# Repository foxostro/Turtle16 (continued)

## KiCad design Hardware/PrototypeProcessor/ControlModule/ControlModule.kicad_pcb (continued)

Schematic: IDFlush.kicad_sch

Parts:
C2, C3, C4, C17: 0.1uF; C_0603_1608Metric_Pad1.08x0.95mm_HandSolder
U1, U18: 74HC245; TSSOP-20_4.4x6.5mm_P0.65mm
U2, U17: 74AHCT16245; TSSOP-48_6.1x12.5mm_P0.5mm

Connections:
/ID/Ctl_Mid0: U17.47 (1A1); also elsewhere on the board
/ID/Ctl_Mid1: U17.46 (1A2); also elsewhere on the board
/ID/Ctl_Mid2: U17.44 (1A3); also elsewhere on the board
/ID/Ctl_Mid3: U17.43 (1A4); also elsewhere on the board
/ID/Ctl_Mid4: U17.41 (1A5); also elsewhere on the board
/ID/Ctl_Mid5: U17.40 (1A6); also elsewhere on the board
/ID/Ctl_Mid6: U17.38 (1A7); also elsewhere on the board
/ID/Ctl_Mid7: U17.37 (1A8); also elsewhere on the board
/ID/Ctl_Mid8: U17.36 (2A1); also elsewhere on the board
/ID/Ctl_Mid9: U17.35 (2A2); also elsewhere on the board
/ID/Ctl_Mid10: U17.33 (2A3); also elsewhere on the board
/ID/Ctl_Mid11: U17.32 (2A4); also elsewhere on the board
/ID/Ctl_Mid12: U17.30 (2A5); also elsewhere on the board
/ID/Ctl_Mid13: U17.29 (2A6); also elsewhere on the board
/ID/Ctl_Mid14: U17.27 (2A7); also elsewhere on the board
/ID/Ctl_Mid15: U17.26 (2A8); also elsewhere on the board
/ID/Ctl_Mid16: U18.11 (B7); also elsewhere on the board
/ID/Ctl_Mid17: U18.12 (B6); also elsewhere on the board
/ID/Ctl_Mid18: U18.13 (B5); also elsewhere on the board
/ID/Ctl_Mid19: U18.14 (B4); also elsewhere on the board
/ID/Ctl_Mid20: U18.15 (B3); also elsewhere on the board
/ID/Ctl_Mid21: U18.16 (B2); also elsewhere on the board
/ID/Ctl_Mid22: U18.17 (B1); also elsewhere on the board
/ID/Ctl_Mid23: U18.18 (B0); also elsewhere on the board
/ID/Hazard Control/FLUSH: U17.25 (2~OE), U17.48 (1~OE), U18.19 (CE); also elsewhere on the board
/ID/Hazard Control/~FLUSH: U1.19 (CE), U2.25 (2~OE), U2.48 (1~OE); also elsewhere on the board
/ID/ID Flush/Ctl_ID0: U2.47 (1A1), U17.2 (1B1); also elsewhere on the board
/ID/ID Flush/Ctl_ID1: U2.46 (1A2), U17.3 (1B2); also elsewhere on the board
/ID/ID Flush/Ctl_ID2: U2.44 (1A3), U17.5 (1B3); also elsewhere on the board
/ID/ID Flush/Ctl_ID3: U2.43 (1A4), U17.6 (1B4); also elsewhere on the board
/ID/ID Flush/Ctl_ID4: U2.41 (1A5), U17.8 (1B5); also elsewhere on the board
/ID/ID Flush/Ctl_ID5: U2.40 (1A6), U17.9 (1B6); also elsewhere on the board
/ID/ID Flush/Ctl_ID6: U2.38 (1A7), U17.11 (1B7); also elsewhere on the board
/ID/ID Flush/Ctl_ID7: U2.37 (1A8), U17.12 (1B8); also elsewhere on the board
/ID/ID Flush/Ctl_ID8: U2.36 (2A1), U17.13 (2B1); also elsewhere on the board
/ID/ID Flush/Ctl_ID9: U2.35 (2A2), U17.14 (2B2); also elsewhere on the board
/ID/ID Flush/Ctl_ID10: U2.33 (2A3), U17.16 (2B3); also elsewhere on the board
/ID/ID Flush/Ctl_ID11: U2.32 (2A4), U17.17 (2B4); also elsewhere on the board
/ID/ID Flush/Ctl_ID12: U2.30 (2A5), U17.19 (2B5); also elsewhere on the board
/ID/ID Flush/Ctl_ID13: U2.29 (2A6), U17.20 (2B6); also elsewhere on the board
/ID/ID Flush/Ctl_ID14: U2.27 (2A7), U17.22 (2B7); also elsewhere on the board
/ID/ID Flush/Ctl_ID15: U2.26 (2A8), U17.23 (2B8); also elsewhere on the board
/ID/ID Flush/Ctl_ID16: U1.11 (B7), U18.9 (A7); also elsewhere on the board
/ID/ID Flush/Ctl_ID17: U1.12 (B6), U18.8 (A6); also elsewhere on the board
/ID/ID Flush/Ctl_ID18: U1.13 (B5), U18.7 (A5); also elsewhere on the board
/ID/ID Flush/Ctl_ID19: U1.14 (B4), U18.6 (A4); also elsewhere on the board
/ID/ID Flush/Ctl_ID20: U1.15 (B3), U18.5 (A3); also elsewhere on the board
/ID/ID Flush/Ctl_ID21: U1.16 (B2), U18.4 (A2); also elsewhere on the board
/ID/ID Flush/Ctl_ID22: U1.17 (B1), U18.3 (A1); also elsewhere on the board
/ID/ID Flush/Ctl_ID23: U1.18 (B0), U18.2 (A0); also elsewhere on the board
GND: C2.2, C3.2, C4.2, C17.2, U1.10 (GND), U2.1 (1DIR), U2.4 (GND), U2.10 (GND), U2.15 (GND), U2.21 (GND), U2.24 (2DIR), U2.28 (GND), U2.34 (GND), U2.39 (GND), U2.45 (GND), U17.4 (GND), U17.10 (GND), U17.15 (GND), U17.21 (GND), U17.28 (GND), U17.34 (GND), U17.39 (GND), U17.45 (GND), U18.1 (A->B), U18.10 (GND); also elsewhere on the board
VCC: C2.1, C3.1, C4.1, C17.1, U1.1 (A->B), U1.2 (A0), U1.3 (A1), U1.4 (A2), U1.5 (A3), U1.6 (A4), U1.7 (A5), U1.8 (A6), U1.9 (A7), U1.20 (VCC), U2.2 (1B1), U2.3 (1B2), U2.5 (1B3), U2.6 (1B4), U2.7 (VCC), U2.8 (1B5), U2.9 (1B6), U2.11 (1B7), U2.12 (1B8), U2.13 (2B1), U2.14 (2B2), U2.16 (2B3), U2.17 (2B4), U2.18 (VCC), U2.19 (2B5), U2.20 (2B6), U2.22 (2B7), U2.23 (2B8), U2.31 (VCC), U2.42 (VCC), U17.1 (1DIR), U17.7 (VCC), U17.18 (VCC), U17.24 (2DIR), U17.31 (VCC), U17.42 (VCC), U18.20 (VCC); also elsewhere on the board

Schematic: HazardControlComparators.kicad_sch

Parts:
C10, C11, C12, C13: 0.1uF; C_0603_1608Metric_Pad1.08x0.95mm_HandSolder
TP34: SEL_B_MATCHES_SEL_C_MEM; TestPoint_Pad_D1.0mm
TP35: SEL_A_MATCHES_SEL_C_MEM; TestPoint_Pad_D1.0mm
TP36: SEL_A_MATCHES_SEL_C_EX; TestPoint_Pad_D1.0mm
TP37: SEL_B_MATCHES_SEL_C_EX; TestPoint_Pad_D1.0mm
U10, U11, U12, U13: 74F521; SOIC-20W_7.5x12.8mm_P1.27mm

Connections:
/ID Prototype Inputs/Ins_ID2: U11.2 (P0), U12.2 (P0); also elsewhere on the board
/ID Prototype Inputs/Ins_ID3: U11.4 (P1), U12.4 (P1); also elsewhere on the board
/ID Prototype Inputs/Ins_ID4: U11.6 (P2), U12.6 (P2); also elsewhere on the board
/ID Prototype Inputs/Ins_ID5: U10.2 (P0), U13.2 (P0); also elsewhere on the board
/ID Prototype Inputs/Ins_ID6: U10.4 (P1), U13.4 (P1); also elsewhere on the board
/ID Prototype Inputs/Ins_ID7: U10.6 (P2), U13.6 (P2); also elsewhere on the board
/ID Prototype Inputs/SelC_MEM0: U12.3 (Q0), U13.3 (Q0); also elsewhere on the board
/ID Prototype Inputs/SelC_MEM1: U12.5 (Q1), U13.5 (Q1); also elsewhere on the board
/ID Prototype Inputs/SelC_MEM2: U12.7 (Q2), U13.7 (Q2); also elsewhere on the board
/ID Prototype Outputs/Ins_EX8: U10.3 (Q0), U11.3 (Q0); also elsewhere on the board
/ID Prototype Outputs/Ins_EX9: U10.5 (Q1), U11.5 (Q1); also elsewhere on the board
/ID Prototype Outputs/Ins_EX10: U10.7 (Q2), U11.7 (Q2); also elsewhere on the board
/ID/Hazard Control/Hazard Control Comparators/SEL_A_MATCHES_SEL_C_EX: TP36.1, U10.19 (~P=Q); also elsewhere on the board
/ID/Hazard Control/Hazard Control Comparators/SEL_A_MATCHES_SEL_C_MEM: TP35.1, U13.19 (~P=Q); also elsewhere on the board
/ID/Hazard Control/Hazard Control Comparators/SEL_B_MATCHES_SEL_C_EX: TP37.1, U11.19 (~P=Q); also elsewhere on the board
/ID/Hazard Control/Hazard Control Comparators/SEL_B_MATCHES_SEL_C_MEM: TP34.1, U12.19 (~P=Q); also elsewhere on the board
GND: C10.2, C11.2, C12.2, C13.2, U10.1 (~OE), U10.8 (P3), U10.9 (Q3), U10.10 (GND), U10.11 (P4), U10.12 (Q4), U10.13 (P5), U10.14 (Q5), U10.15 (P6), U10.16 (Q6), U10.17 (P7), U10.18 (Q7), U11.1 (~OE), U11.8 (P3), U11.9 (Q3), U11.10 (GND), U11.11 (P4), U11.12 (Q4), U11.13 (P5), U11.14 (Q5), U11.15 (P6), U11.16 (Q6), U11.17 (P7), U11.18 (Q7), U12.1 (~OE), U12.8 (P3), U12.9 (Q3), U12.10 (GND), U12.11 (P4), U12.12 (Q4), U12.13 (P5), U12.14 (Q5), U12.15 (P6), U12.16 (Q6), U12.17 (P7), U12.18 (Q7), U13.1 (~OE), U13.8 (P3), U13.9 (Q3), U13.10 (GND), U13.11 (P4), U13.12 (Q4), U13.13 (P5), U13.14 (Q5), U13.15 (P6), U13.16 (Q6), U13.17 (P7), U13.18 (Q7); also elsewhere on the board
VCC: C10.1, C11.1, C12.1, C13.1, U10.20 (VCC), U11.20 (VCC), U12.20 (VCC), U13.20 (VCC); also elsewhere on the board

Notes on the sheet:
SelA0
SelB1
SelA2
SelA1
SelB2
SelB0

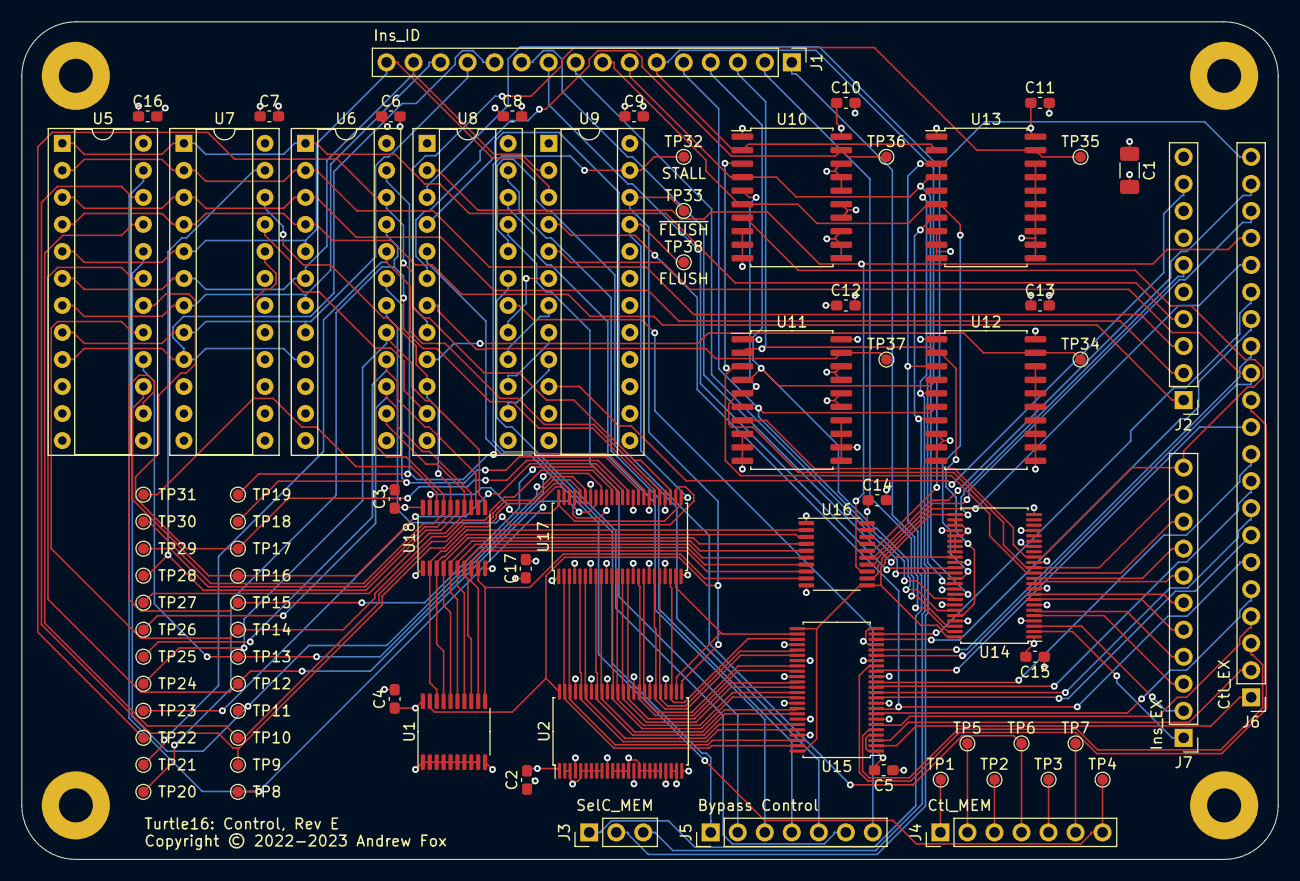
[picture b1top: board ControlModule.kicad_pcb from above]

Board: 4 copper layers, 118.1 x 78.7 mm, 82 parts (0 on the bottom side), 131 nets.

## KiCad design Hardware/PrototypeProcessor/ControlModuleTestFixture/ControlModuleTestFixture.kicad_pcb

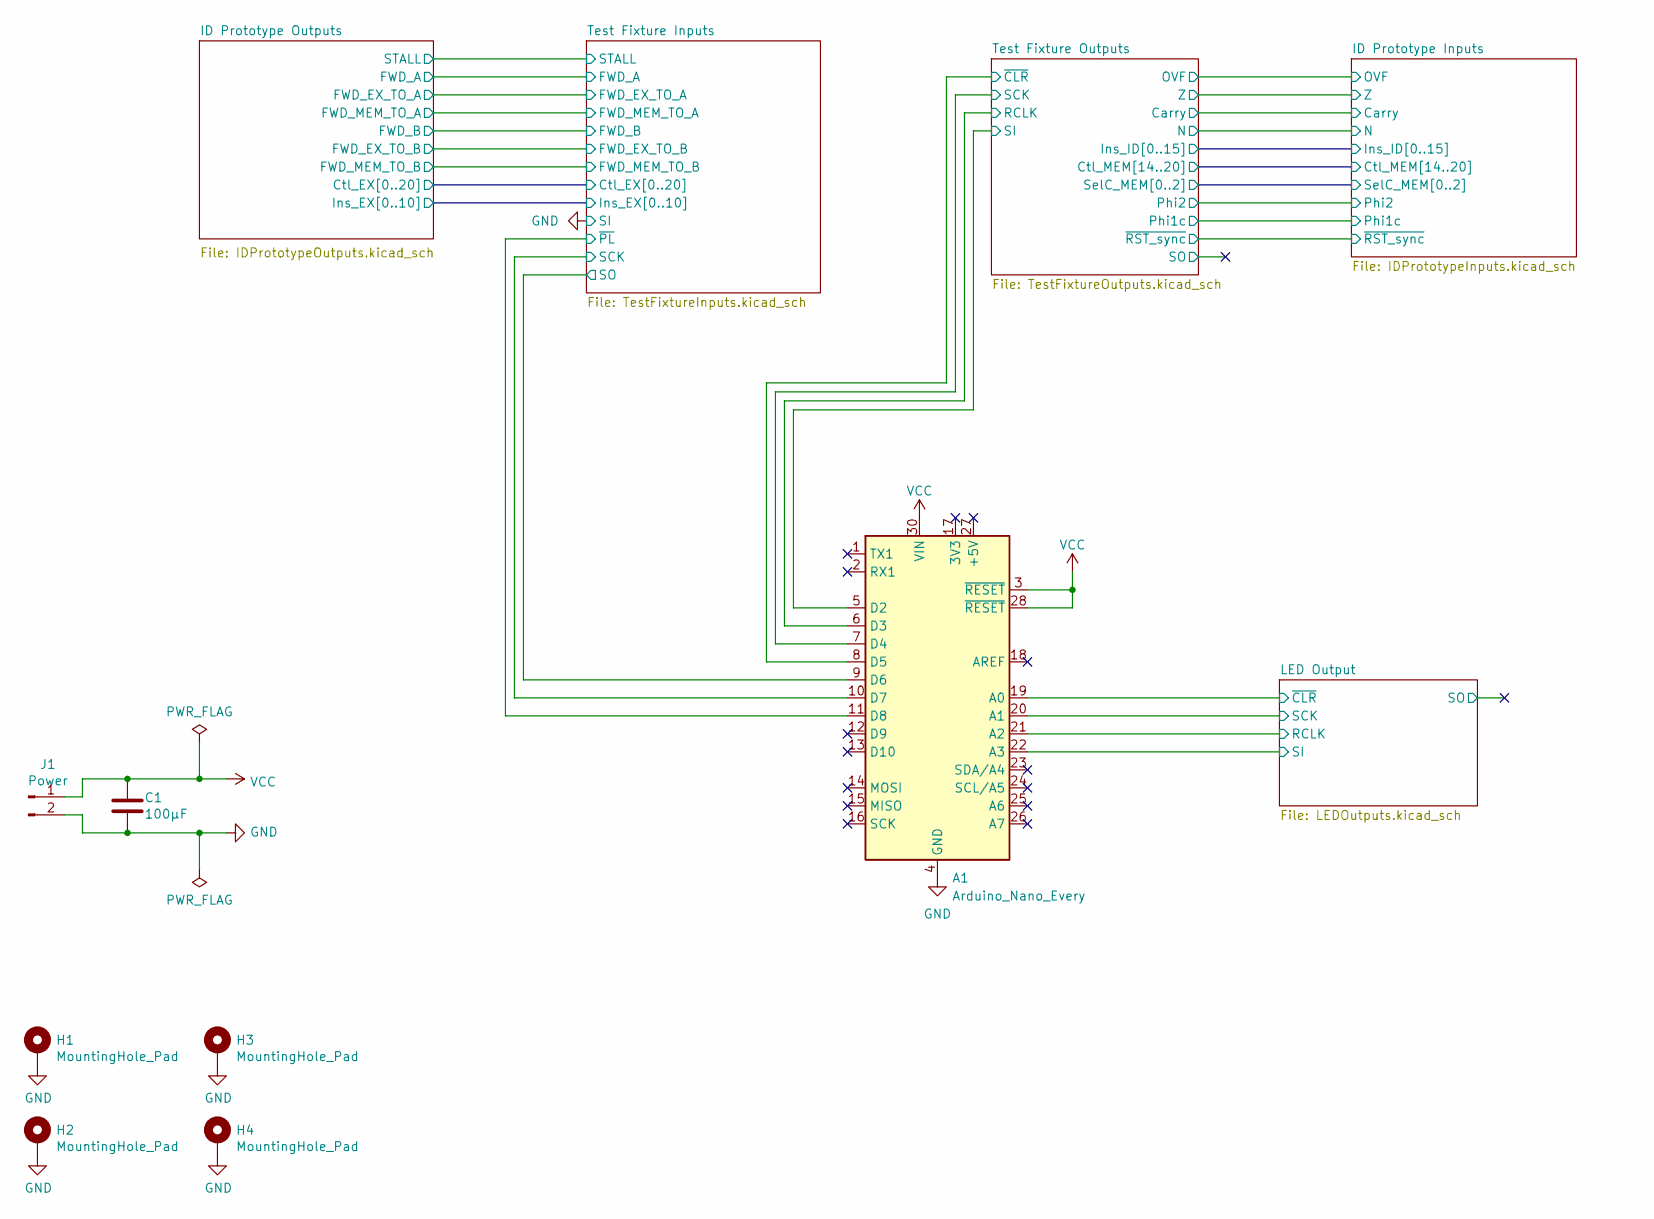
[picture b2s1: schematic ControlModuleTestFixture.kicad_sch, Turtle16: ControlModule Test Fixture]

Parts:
A1: Arduino_Nano_Every; Arduino_Nano
C1: 100µF; C_1206_3216Metric_Pad1.33x1.80mm_HandSolder
H1, H2, H3, H4: MountingHole_Pad; MountingHole_3.2mm_M3_Pad
J1: Power; 172448-0002

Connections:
/LED Output/RCLK: A1.21 (A2); also elsewhere on the board
/LED Output/SCK: A1.20 (A1); also elsewhere on the board
/LED Output/SI: A1.22 (A3); also elsewhere on the board
/LED Output/~CLR: A1.19 (A0); also elsewhere on the board
/Test Fixture Inputs/SCK: A1.10 (D7); also elsewhere on the board
/Test Fixture Inputs/SO: A1.9 (D6); also elsewhere on the board
/Test Fixture Inputs/~PL: A1.11 (D8); also elsewhere on the board
/Test Fixture Outputs/RCLK: A1.6 (D3); also elsewhere on the board
/Test Fixture Outputs/SCK: A1.7 (D4); also elsewhere on the board
/Test Fixture Outputs/SI: A1.5 (D2); also elsewhere on the board
/Test Fixture Outputs/~CLR: A1.8 (D5); also elsewhere on the board
GND: A1.4 (GND), A1.29 (GND), C1.2, H1.1, H2.1, H3.1, H4.1, J1.2; also elsewhere on the board
VCC: A1.3 (~RESET), A1.28 (~RESET), A1.30 (VIN), C1.1, J1.1; also elsewhere on the board

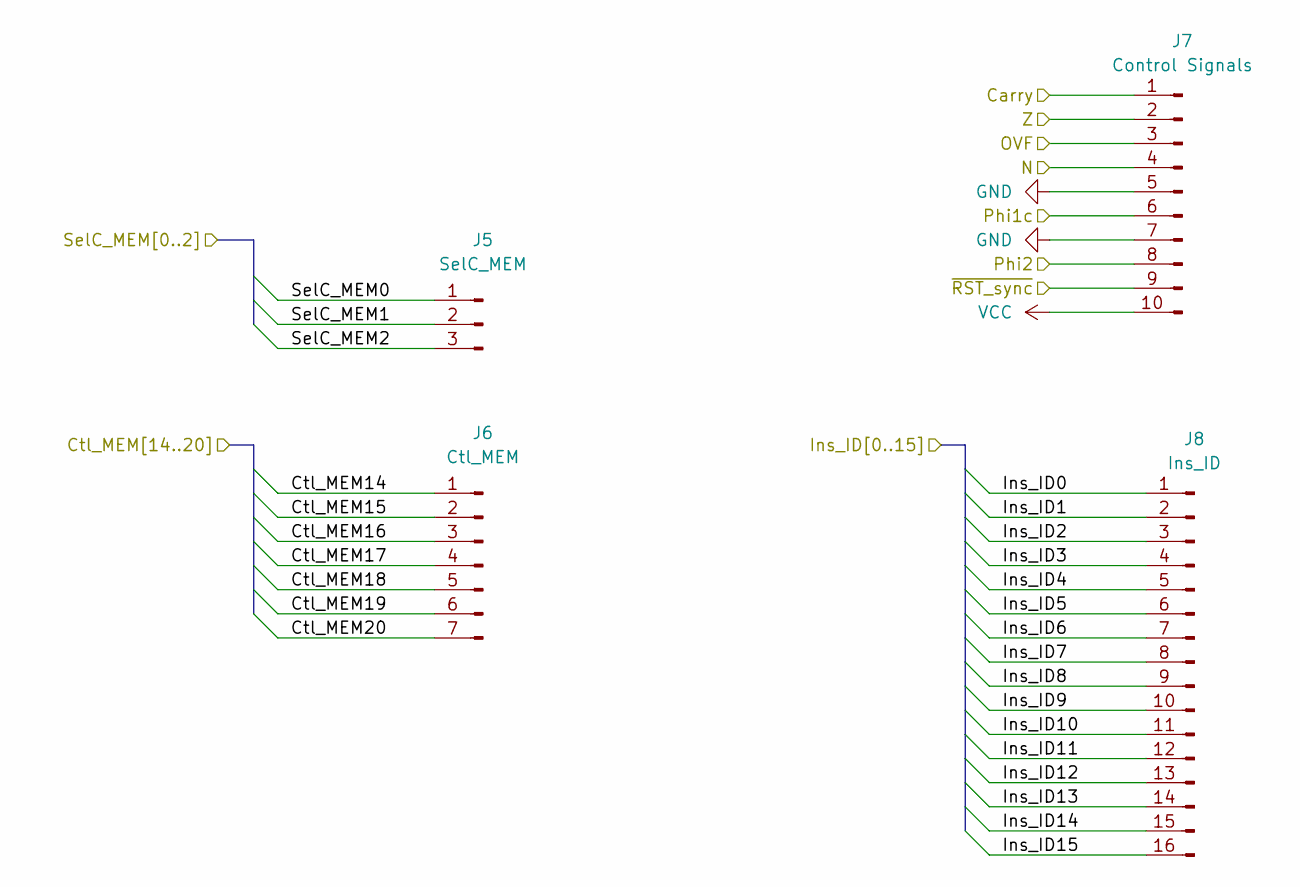
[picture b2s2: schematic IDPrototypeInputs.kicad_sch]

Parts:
J5: SelC_MEM; PinHeader_1x03_P2.54mm_Vertical
J6: Ctl_MEM; PinHeader_1x07_P2.54mm_Vertical
J7: Control Signals; PinHeader_1x10_P2.54mm_Vertical
J8: Ins_ID; PinHeader_1x16_P2.54mm_Vertical

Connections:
/ID Prototype Inputs/Carry: J7.1; also elsewhere on the board
/ID Prototype Inputs/Ctl_MEM14: J6.1; also elsewhere on the board
/ID Prototype Inputs/Ctl_MEM15: J6.2; also elsewhere on the board
/ID Prototype Inputs/Ctl_MEM16: J6.3; also elsewhere on the board
/ID Prototype Inputs/Ctl_MEM17: J6.4; also elsewhere on the board
/ID Prototype Inputs/Ctl_MEM18: J6.5; also elsewhere on the board
/ID Prototype Inputs/Ctl_MEM19: J6.6; also elsewhere on the board
/ID Prototype Inputs/Ctl_MEM20: J6.7; also elsewhere on the board
/ID Prototype Inputs/Ins_ID0: J8.1; also elsewhere on the board
/ID Prototype Inputs/Ins_ID1: J8.2; also elsewhere on the board
/ID Prototype Inputs/Ins_ID2: J8.3; also elsewhere on the board
/ID Prototype Inputs/Ins_ID3: J8.4; also elsewhere on the board
/ID Prototype Inputs/Ins_ID4: J8.5; also elsewhere on the board
/ID Prototype Inputs/Ins_ID5: J8.6; also elsewhere on the board
/ID Prototype Inputs/Ins_ID6: J8.7; also elsewhere on the board
/ID Prototype Inputs/Ins_ID7: J8.8; also elsewhere on the board
/ID Prototype Inputs/Ins_ID8: J8.9; also elsewhere on the board
/ID Prototype Inputs/Ins_ID9: J8.10; also elsewhere on the board
/ID Prototype Inputs/Ins_ID10: J8.11; also elsewhere on the board
/ID Prototype Inputs/Ins_ID11: J8.12; also elsewhere on the board
/ID Prototype Inputs/Ins_ID12: J8.13; also elsewhere on the board
/ID Prototype Inputs/Ins_ID13: J8.14; also elsewhere on the board
/ID Prototype Inputs/Ins_ID14: J8.15; also elsewhere on the board
/ID Prototype Inputs/Ins_ID15: J8.16; also elsewhere on the board
/ID Prototype Inputs/N: J7.4; also elsewhere on the board
/ID Prototype Inputs/OVF: J7.3; also elsewhere on the board
/ID Prototype Inputs/Phi1c: J7.6; also elsewhere on the board
/ID Prototype Inputs/Phi2: J7.8; also elsewhere on the board
/ID Prototype Inputs/SelC_MEM0: J5.1; also elsewhere on the board
/ID Prototype Inputs/SelC_MEM1: J5.2; also elsewhere on the board
/ID Prototype Inputs/SelC_MEM2: J5.3; also elsewhere on the board
/ID Prototype Inputs/Z: J7.2; also elsewhere on the board
/ID Prototype Inputs/~RST_sync: J7.9; also elsewhere on the board
GND: J7.5, J7.7; also elsewhere on the board
VCC: J7.10; also elsewhere on the board

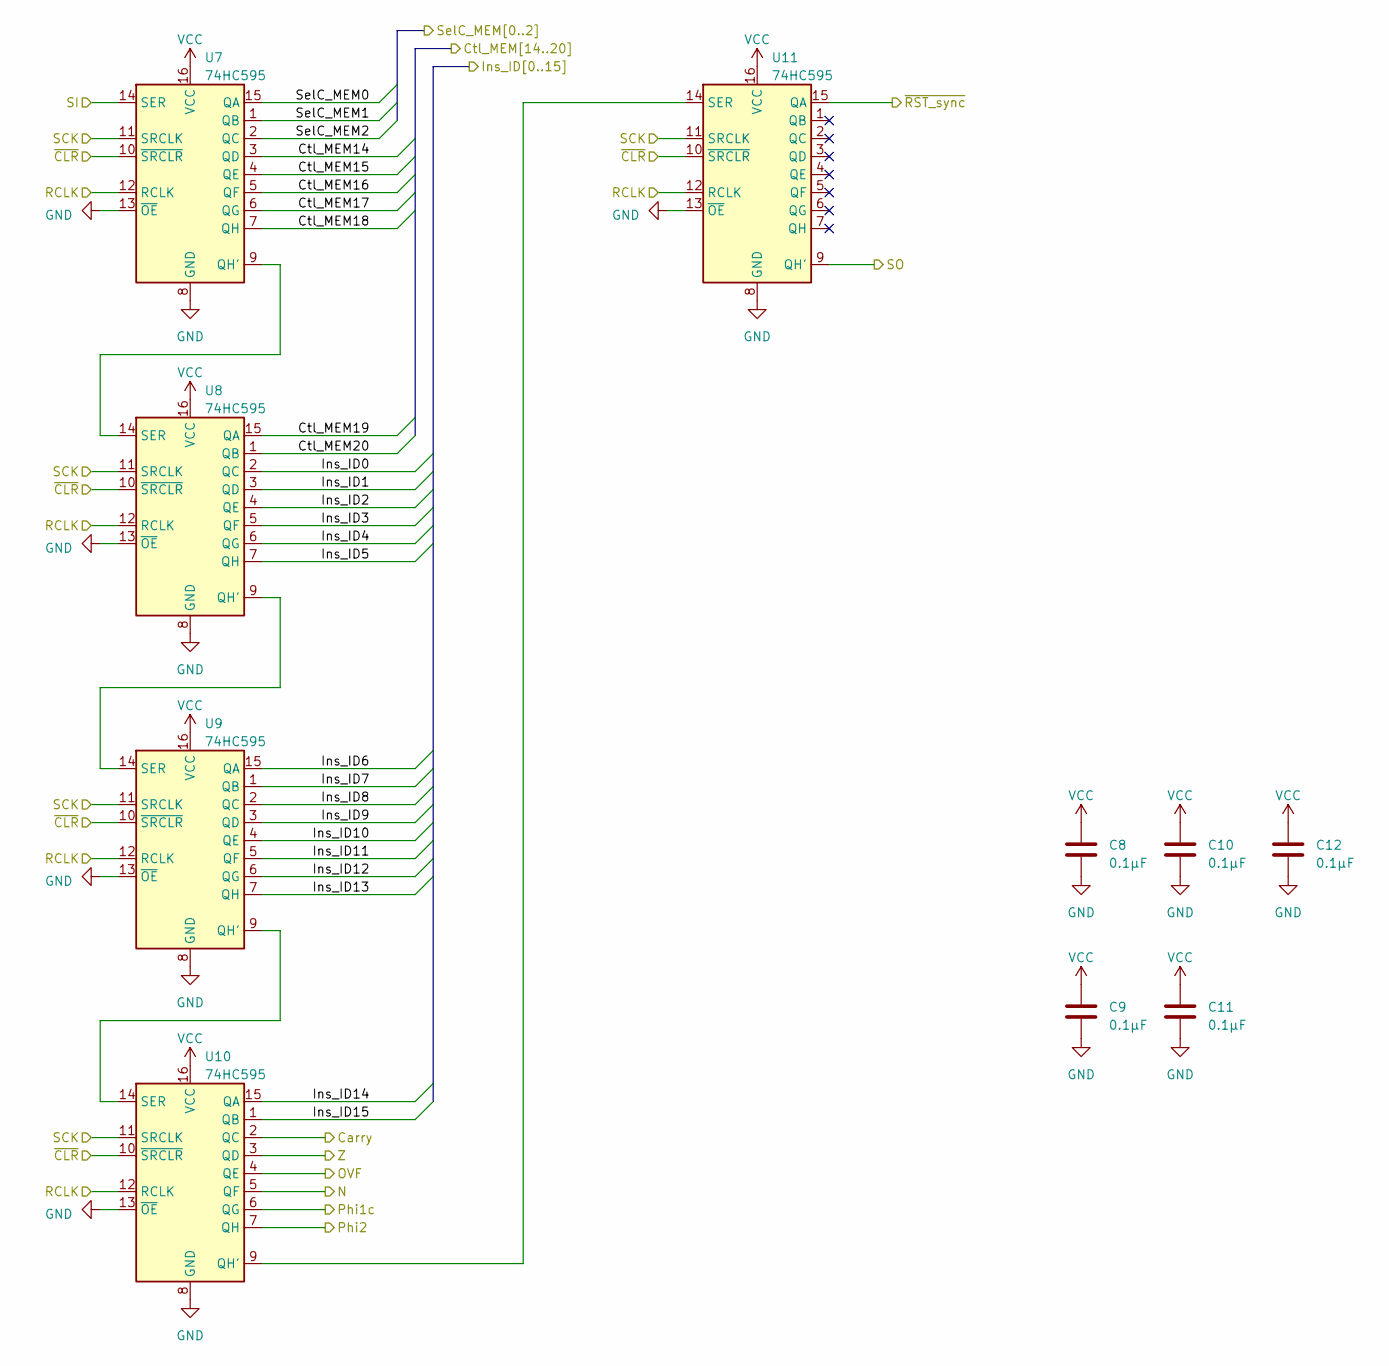
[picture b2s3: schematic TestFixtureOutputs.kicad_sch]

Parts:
C8, C9, C10, C11, C12: 0.1µF; C_0603_1608Metric
U7, U8, U9, U10, U11: 74HC595; TSSOP-16_4.4x5mm_P0.65mm

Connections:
/ID Prototype Inputs/Carry: U10.2 (QC); also elsewhere on the board
/ID Prototype Inputs/Ctl_MEM14: U7.3 (QD); also elsewhere on the board
/ID Prototype Inputs/Ctl_MEM15: U7.4 (QE); also elsewhere on the board
/ID Prototype Inputs/Ctl_MEM16: U7.5 (QF); also elsewhere on the board
/ID Prototype Inputs/Ctl_MEM17: U7.6 (QG); also elsewhere on the board
/ID Prototype Inputs/Ctl_MEM18: U7.7 (QH); also elsewhere on the board
/ID Prototype Inputs/Ctl_MEM19: U8.15 (QA); also elsewhere on the board
/ID Prototype Inputs/Ctl_MEM20: U8.1 (QB); also elsewhere on the board
/ID Prototype Inputs/Ins_ID0: U8.2 (QC); also elsewhere on the board
/ID Prototype Inputs/Ins_ID1: U8.3 (QD); also elsewhere on the board
/ID Prototype Inputs/Ins_ID2: U8.4 (QE); also elsewhere on the board
/ID Prototype Inputs/Ins_ID3: U8.5 (QF); also elsewhere on the board
/ID Prototype Inputs/Ins_ID4: U8.6 (QG); also elsewhere on the board
/ID Prototype Inputs/Ins_ID5: U8.7 (QH); also elsewhere on the board
/ID Prototype Inputs/Ins_ID6: U9.15 (QA); also elsewhere on the board
/ID Prototype Inputs/Ins_ID7: U9.1 (QB); also elsewhere on the board
/ID Prototype Inputs/Ins_ID8: U9.2 (QC); also elsewhere on the board
/ID Prototype Inputs/Ins_ID9: U9.3 (QD); also elsewhere on the board
/ID Prototype Inputs/Ins_ID10: U9.4 (QE); also elsewhere on the board
/ID Prototype Inputs/Ins_ID11: U9.5 (QF); also elsewhere on the board
/ID Prototype Inputs/Ins_ID12: U9.6 (QG); also elsewhere on the board
/ID Prototype Inputs/Ins_ID13: U9.7 (QH); also elsewhere on the board
/ID Prototype Inputs/Ins_ID14: U10.15 (QA); also elsewhere on the board
/ID Prototype Inputs/Ins_ID15: U10.1 (QB); also elsewhere on the board
/ID Prototype Inputs/N: U10.5 (QF); also elsewhere on the board
/ID Prototype Inputs/OVF: U10.4 (QE); also elsewhere on the board
/ID Prototype Inputs/Phi1c: U10.6 (QG); also elsewhere on the board
/ID Prototype Inputs/Phi2: U10.7 (QH); also elsewhere on the board
/ID Prototype Inputs/SelC_MEM0: U7.15 (QA); also elsewhere on the board
/ID Prototype Inputs/SelC_MEM1: U7.1 (QB); also elsewhere on the board
/ID Prototype Inputs/SelC_MEM2: U7.2 (QC); also elsewhere on the board
/ID Prototype Inputs/Z: U10.3 (QD); also elsewhere on the board
/ID Prototype Inputs/~RST_sync: U11.15 (QA); also elsewhere on the board
/Test Fixture Outputs/RCLK: U7.12 (RCLK), U8.12 (RCLK), U9.12 (RCLK), U10.12 (RCLK), U11.12 (RCLK); also elsewhere on the board
/Test Fixture Outputs/SCK: U7.11 (SRCLK), U8.11 (SRCLK), U9.11 (SRCLK), U10.11 (SRCLK), U11.11 (SRCLK); also elsewhere on the board
/Test Fixture Outputs/SI: U7.14 (SER); also elsewhere on the board
/Test Fixture Outputs/SO: U11.9 (QH')
/Test Fixture Outputs/~CLR: U7.10 (~SRCLR), U8.10 (~SRCLR), U9.10 (~SRCLR), U10.10 (~SRCLR), U11.10 (~SRCLR); also elsewhere on the board
GND: C8.2, C9.2, C10.2, C11.2, C12.2, U7.8 (GND), U7.13 (~OE), U8.8 (GND), U8.13 (~OE), U9.8 (GND), U9.13 (~OE), U10.8 (GND), U10.13 (~OE), U11.8 (GND), U11.13 (~OE); also elsewhere on the board
unnamed: U7.9 (QH'), U8.14 (SER)
unnamed: U8.9 (QH'), U9.14 (SER)
unnamed: U10.9 (QH'), U11.14 (SER)
unnamed: U9.9 (QH'), U10.14 (SER)
VCC: C8.1, C9.1, C10.1, C11.1, C12.1, U7.16 (VCC), U8.16 (VCC), U9.16 (VCC), U10.16 (VCC), U11.16 (VCC); also elsewhere on the board

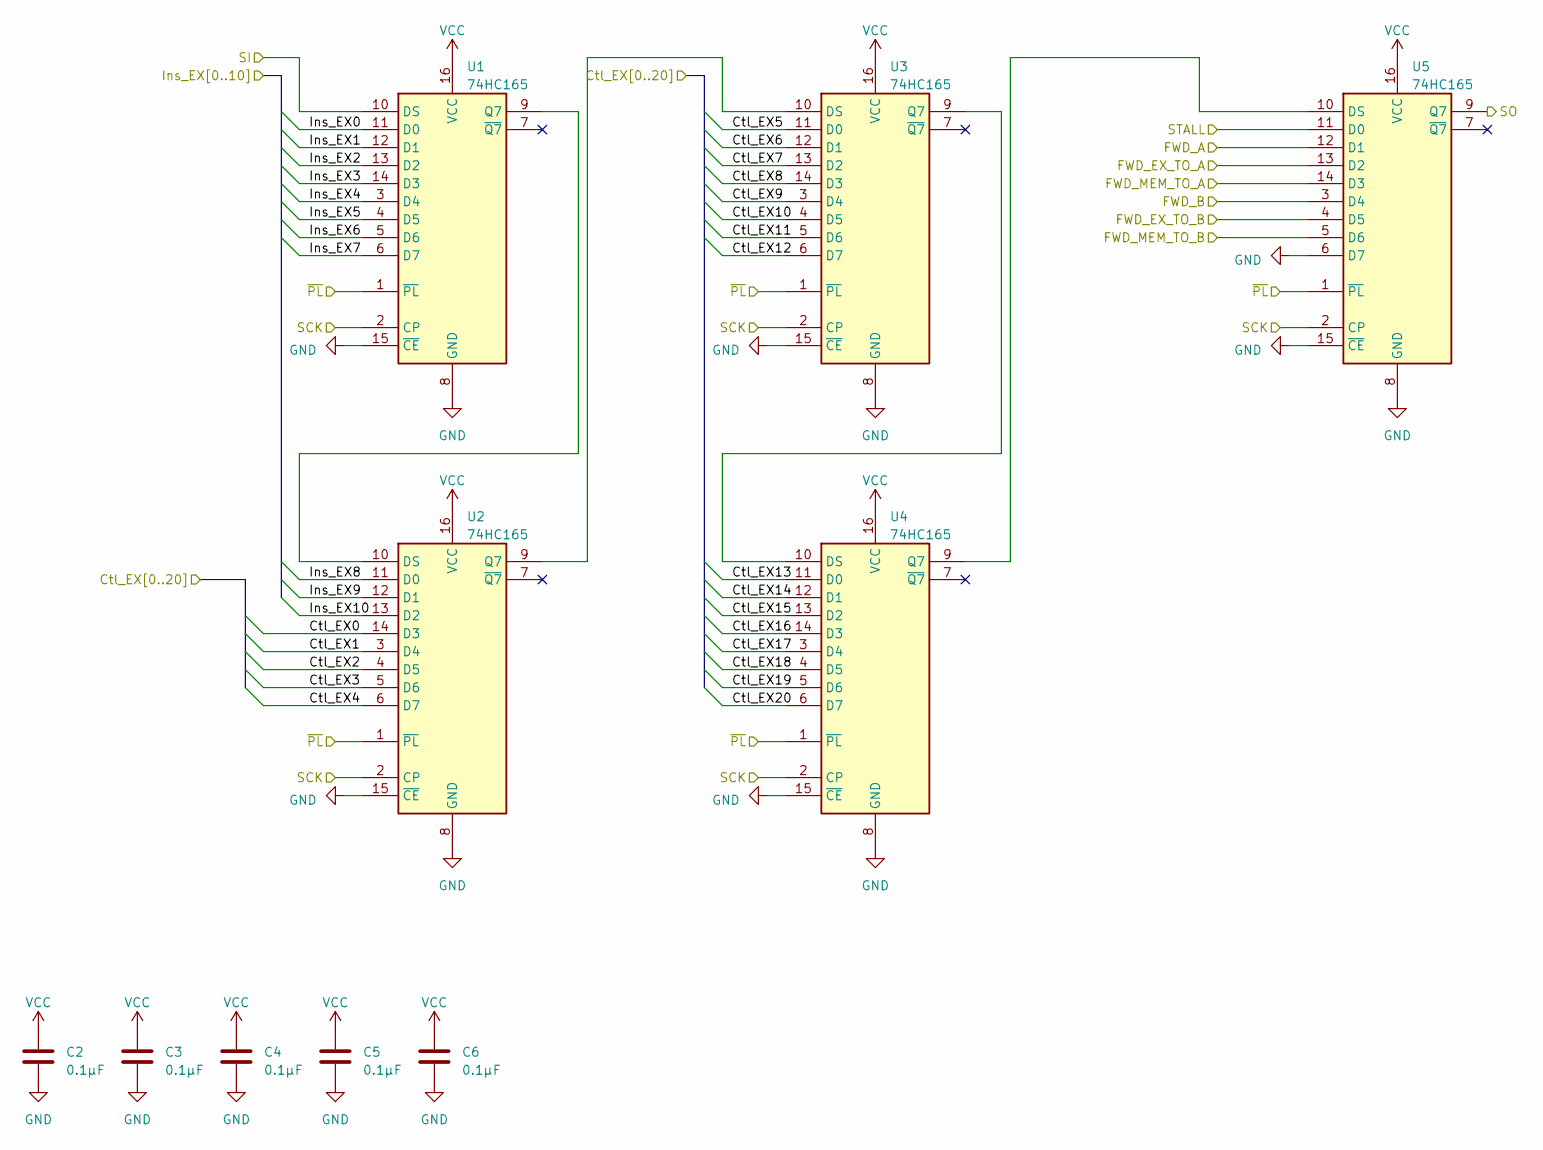
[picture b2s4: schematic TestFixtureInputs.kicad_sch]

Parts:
C2, C3, C4, C5, C6: 0.1µF; C_0603_1608Metric
U1, U2, U3, U4, U5: 74HC165; TSSOP-16_4.4x5mm_P0.65mm

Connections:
/ID Prototype Outputs/Ctl_EX0: U2.14 (D3); also elsewhere on the board
/ID Prototype Outputs/Ctl_EX1: U2.3 (D4); also elsewhere on the board
/ID Prototype Outputs/Ctl_EX2: U2.4 (D5); also elsewhere on the board
/ID Prototype Outputs/Ctl_EX3: U2.5 (D6); also elsewhere on the board
/ID Prototype Outputs/Ctl_EX4: U2.6 (D7); also elsewhere on the board
/ID Prototype Outputs/Ctl_EX5: U3.11 (D0); also elsewhere on the board
/ID Prototype Outputs/Ctl_EX6: U3.12 (D1); also elsewhere on the board
/ID Prototype Outputs/Ctl_EX7: U3.13 (D2); also elsewhere on the board
/ID Prototype Outputs/Ctl_EX8: U3.14 (D3); also elsewhere on the board
/ID Prototype Outputs/Ctl_EX9: U3.3 (D4); also elsewhere on the board
/ID Prototype Outputs/Ctl_EX10: U3.4 (D5); also elsewhere on the board
/ID Prototype Outputs/Ctl_EX11: U3.5 (D6); also elsewhere on the board
/ID Prototype Outputs/Ctl_EX12: U3.6 (D7); also elsewhere on the board
/ID Prototype Outputs/Ctl_EX13: U4.11 (D0); also elsewhere on the board
/ID Prototype Outputs/Ctl_EX14: U4.12 (D1); also elsewhere on the board
/ID Prototype Outputs/Ctl_EX15: U4.13 (D2); also elsewhere on the board
/ID Prototype Outputs/Ctl_EX16: U4.14 (D3); also elsewhere on the board
/ID Prototype Outputs/Ctl_EX17: U4.3 (D4); also elsewhere on the board
/ID Prototype Outputs/Ctl_EX18: U4.4 (D5); also elsewhere on the board
/ID Prototype Outputs/Ctl_EX19: U4.5 (D6); also elsewhere on the board
/ID Prototype Outputs/Ctl_EX20: U4.6 (D7); also elsewhere on the board
/ID Prototype Outputs/FWD_A: U5.12 (D1); also elsewhere on the board
/ID Prototype Outputs/FWD_B: U5.3 (D4); also elsewhere on the board
/ID Prototype Outputs/FWD_EX_TO_A: U5.13 (D2); also elsewhere on the board
/ID Prototype Outputs/FWD_EX_TO_B: U5.4 (D5); also elsewhere on the board
/ID Prototype Outputs/FWD_MEM_TO_A: U5.14 (D3); also elsewhere on the board
/ID Prototype Outputs/FWD_MEM_TO_B: U5.5 (D6); also elsewhere on the board
/ID Prototype Outputs/Ins_EX0: U1.11 (D0); also elsewhere on the board
/ID Prototype Outputs/Ins_EX1: U1.12 (D1); also elsewhere on the board
/ID Prototype Outputs/Ins_EX2: U1.13 (D2); also elsewhere on the board
/ID Prototype Outputs/Ins_EX3: U1.14 (D3); also elsewhere on the board
/ID Prototype Outputs/Ins_EX4: U1.3 (D4); also elsewhere on the board
/ID Prototype Outputs/Ins_EX5: U1.4 (D5); also elsewhere on the board
/ID Prototype Outputs/Ins_EX6: U1.5 (D6); also elsewhere on the board
/ID Prototype Outputs/Ins_EX7: U1.6 (D7); also elsewhere on the board
/ID Prototype Outputs/Ins_EX8: U2.11 (D0); also elsewhere on the board
/ID Prototype Outputs/Ins_EX9: U2.12 (D1); also elsewhere on the board
/ID Prototype Outputs/Ins_EX10: U2.13 (D2); also elsewhere on the board
/ID Prototype Outputs/STALL: U5.11 (D0); also elsewhere on the board
/Test Fixture Inputs/SCK: U1.2 (CP), U2.2 (CP), U3.2 (CP), U4.2 (CP), U5.2 (CP); also elsewhere on the board
/Test Fixture Inputs/SO: U5.9 (Q7); also elsewhere on the board
/Test Fixture Inputs/~PL: U1.1 (~PL), U2.1 (~PL), U3.1 (~PL), U4.1 (~PL), U5.1 (~PL); also elsewhere on the board
GND: C2.2, C3.2, C4.2, C5.2, C6.2, U1.8 (GND), U1.10 (DS), U1.15 (~CE), U2.8 (GND), U2.15 (~CE), U3.8 (GND), U3.15 (~CE), U4.8 (GND), U4.15 (~CE), U5.6 (D7), U5.8 (GND), U5.15 (~CE); also elsewhere on the board
unnamed: U1.9 (Q7), U2.10 (DS)
unnamed: U2.9 (Q7), U3.10 (DS)
unnamed: U3.9 (Q7), U4.10 (DS)
unnamed: U4.9 (Q7), U5.10 (DS)
VCC: C2.1, C3.1, C4.1, C5.1, C6.1, U1.16 (VCC), U2.16 (VCC), U3.16 (VCC), U4.16 (VCC), U5.16 (VCC); also elsewhere on the board

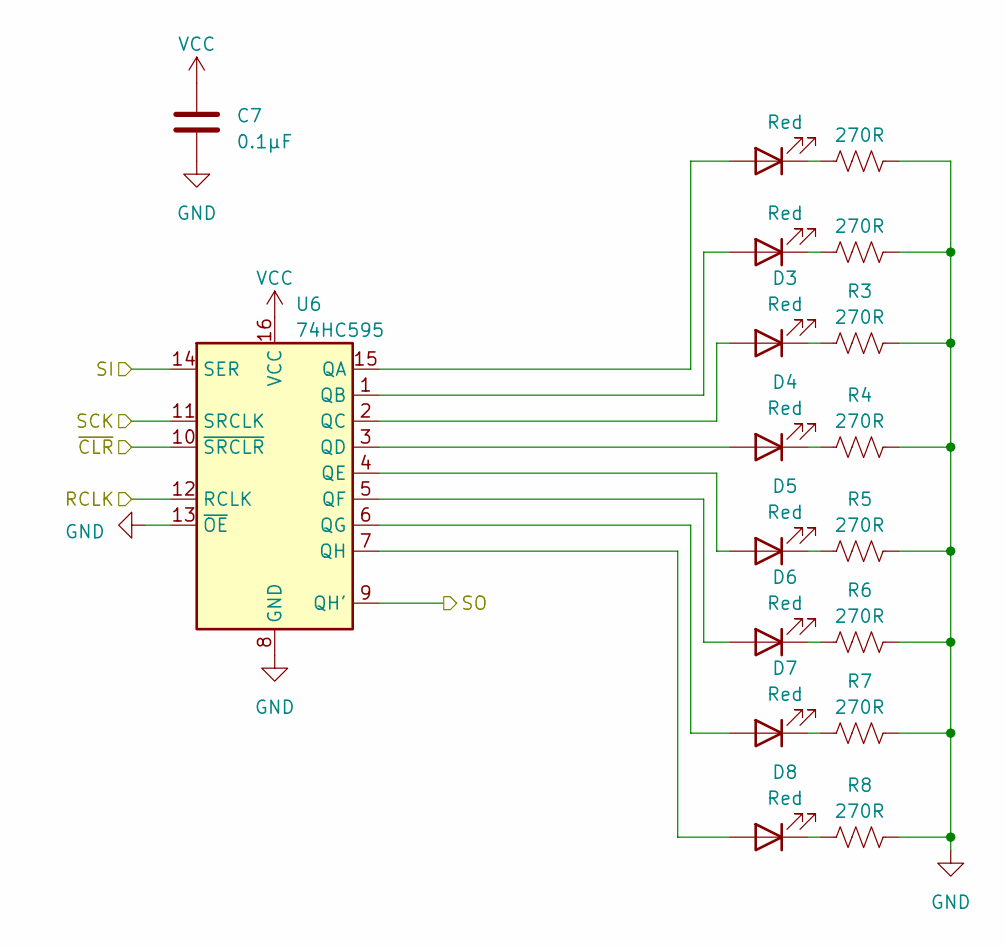
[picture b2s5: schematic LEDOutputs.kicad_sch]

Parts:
C7: 0.1µF; C_0603_1608Metric
D1, D2, D3, D4, D5, D6, D7, D8: Red; LED_0603_1608Metric
R1, R2, R3, R4, R5, R6, R7, R8: 270R; C_0603_1608Metric
U6: 74HC595; TSSOP-16_4.4x5mm_P0.65mm

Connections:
/LED Output/RCLK: U6.12 (RCLK); also elsewhere on the board
/LED Output/SCK: U6.11 (SRCLK); also elsewhere on the board
/LED Output/SI: U6.14 (SER); also elsewhere on the board
/LED Output/SO: U6.9 (QH')
/LED Output/~CLR: U6.10 (~SRCLR); also elsewhere on the board
GND: C7.2, R1.2, R2.2, R3.2, R4.2, R5.2, R6.2, R7.2, R8.2, U6.8 (GND), U6.13 (~OE); also elsewhere on the board
unnamed: D1.2 (A), U6.15 (QA)
unnamed: D1.1 (K), R1.1
unnamed: D2.2 (A), U6.1 (QB)
unnamed: D2.1 (K), R2.1
unnamed: D3.2 (A), U6.2 (QC)
unnamed: D3.1 (K), R3.1
unnamed: D4.2 (A), U6.3 (QD)
unnamed: D4.1 (K), R4.1
unnamed: D5.2 (A), U6.4 (QE)
unnamed: D5.1 (K), R5.1
unnamed: D6.2 (A), U6.5 (QF)
unnamed: D6.1 (K), R6.1
unnamed: D7.2 (A), U6.6 (QG)
unnamed: D7.1 (K), R7.1
unnamed: D8.2 (A), U6.7 (QH)
unnamed: D8.1 (K), R8.1
VCC: C7.1, U6.16 (VCC); also elsewhere on the board

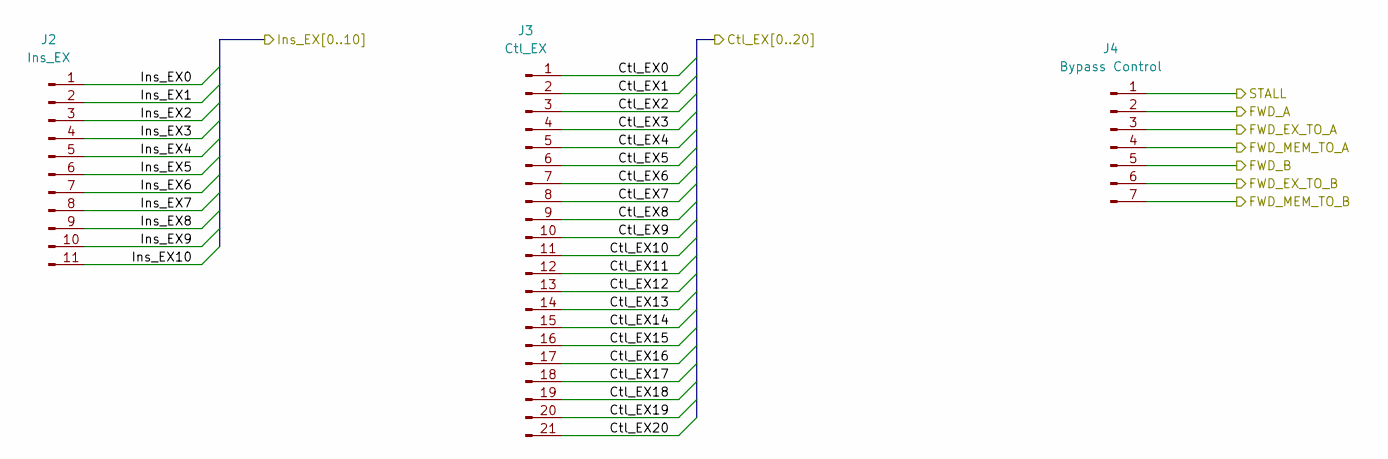
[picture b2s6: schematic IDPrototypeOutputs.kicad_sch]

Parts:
J2: Ins_EX; PinHeader_1x11_P2.54mm_Vertical
J3: Ctl_EX; PinHeader_1x21_P2.54mm_Vertical
J4: Bypass Control; PinHeader_1x07_P2.54mm_Vertical

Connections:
/ID Prototype Outputs/Ctl_EX0: J3.1; also elsewhere on the board
/ID Prototype Outputs/Ctl_EX1: J3.2; also elsewhere on the board
/ID Prototype Outputs/Ctl_EX2: J3.3; also elsewhere on the board
/ID Prototype Outputs/Ctl_EX3: J3.4; also elsewhere on the board
/ID Prototype Outputs/Ctl_EX4: J3.5; also elsewhere on the board
/ID Prototype Outputs/Ctl_EX5: J3.6; also elsewhere on the board
/ID Prototype Outputs/Ctl_EX6: J3.7; also elsewhere on the board
/ID Prototype Outputs/Ctl_EX7: J3.8; also elsewhere on the board
/ID Prototype Outputs/Ctl_EX8: J3.9; also elsewhere on the board
/ID Prototype Outputs/Ctl_EX9: J3.10; also elsewhere on the board
/ID Prototype Outputs/Ctl_EX10: J3.11; also elsewhere on the board
/ID Prototype Outputs/Ctl_EX11: J3.12; also elsewhere on the board
/ID Prototype Outputs/Ctl_EX12: J3.13; also elsewhere on the board
/ID Prototype Outputs/Ctl_EX13: J3.14; also elsewhere on the board
/ID Prototype Outputs/Ctl_EX14: J3.15; also elsewhere on the board
/ID Prototype Outputs/Ctl_EX15: J3.16; also elsewhere on the board
/ID Prototype Outputs/Ctl_EX16: J3.17; also elsewhere on the board
/ID Prototype Outputs/Ctl_EX17: J3.18; also elsewhere on the board
/ID Prototype Outputs/Ctl_EX18: J3.19; also elsewhere on the board
/ID Prototype Outputs/Ctl_EX19: J3.20; also elsewhere on the board
/ID Prototype Outputs/Ctl_EX20: J3.21; also elsewhere on the board
/ID Prototype Outputs/FWD_A: J4.2; also elsewhere on the board
/ID Prototype Outputs/FWD_B: J4.5; also elsewhere on the board
/ID Prototype Outputs/FWD_EX_TO_A: J4.3; also elsewhere on the board
/ID Prototype Outputs/FWD_EX_TO_B: J4.6; also elsewhere on the board
/ID Prototype Outputs/FWD_MEM_TO_A: J4.4; also elsewhere on the board
/ID Prototype Outputs/FWD_MEM_TO_B: J4.7; also elsewhere on the board
/ID Prototype Outputs/Ins_EX0: J2.1; also elsewhere on the board
/ID Prototype Outputs/Ins_EX1: J2.2; also elsewhere on the board
/ID Prototype Outputs/Ins_EX2: J2.3; also elsewhere on the board
/ID Prototype Outputs/Ins_EX3: J2.4; also elsewhere on the board
/ID Prototype Outputs/Ins_EX4: J2.5; also elsewhere on the board
/ID Prototype Outputs/Ins_EX5: J2.6; also elsewhere on the board
/ID Prototype Outputs/Ins_EX6: J2.7; also elsewhere on the board
/ID Prototype Outputs/Ins_EX7: J2.8; also elsewhere on the board
/ID Prototype Outputs/Ins_EX8: J2.9; also elsewhere on the board
/ID Prototype Outputs/Ins_EX9: J2.10; also elsewhere on the board
/ID Prototype Outputs/Ins_EX10: J2.11; also elsewhere on the board
/ID Prototype Outputs/STALL: J4.1; also elsewhere on the board
